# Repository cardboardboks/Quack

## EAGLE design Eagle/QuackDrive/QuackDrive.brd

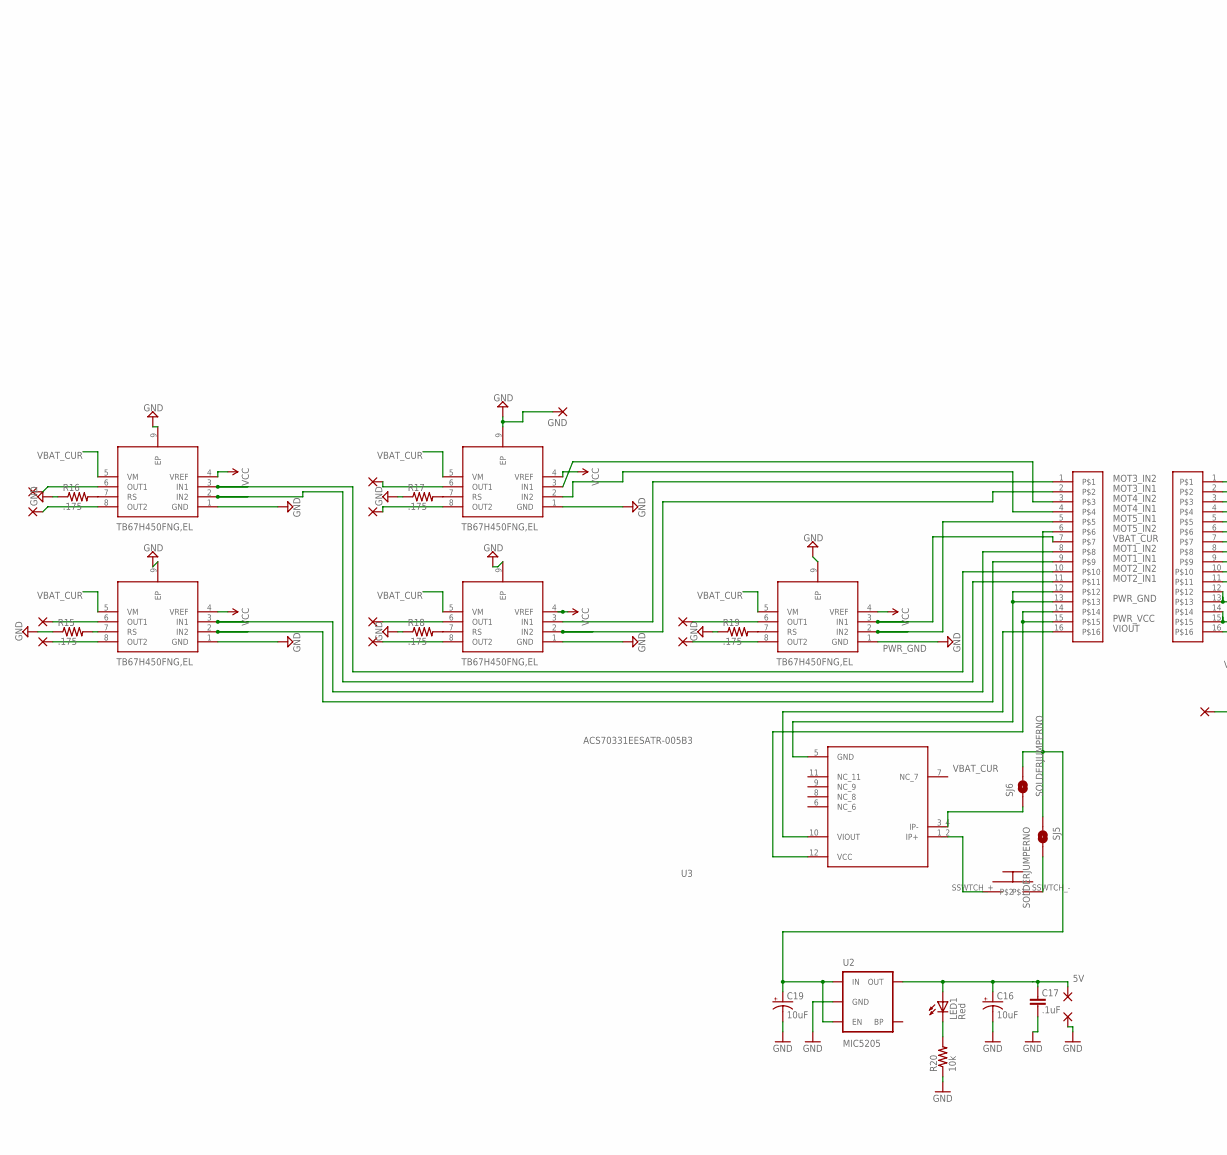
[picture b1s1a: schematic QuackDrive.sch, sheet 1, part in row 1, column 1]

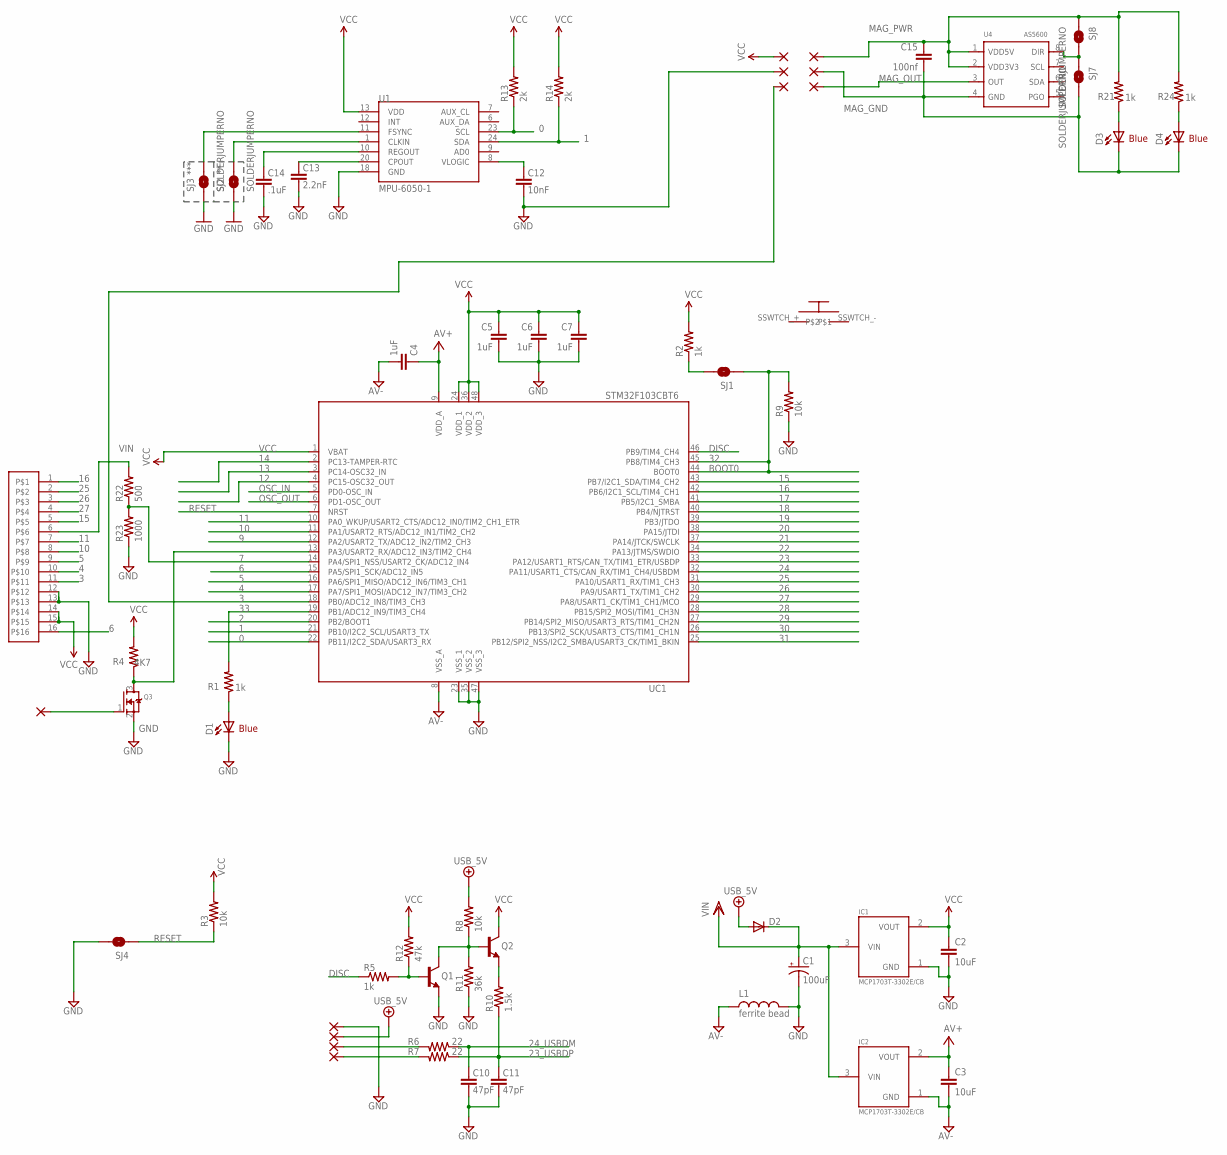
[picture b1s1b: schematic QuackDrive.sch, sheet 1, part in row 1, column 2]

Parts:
C1: 100uF; EIA3216
C2, C3: 10uF; 0805
C4, C5, C6, C7: 1uF; C0402
C10, C11: 47pF; C0402
C12: 10nF; C0402
C13: 2.2nF; C0402
C14, C17: .1uF; C0402
C15: 100nf; C0402
C16, C19: 10uF; EIA3216
D1, D3, D4: Blue; LED-1206
D2: DIODESOD; SOD-323
GND: SMD5; SMD2,54-5,08
IC1, IC2: MCP1703T-3302E/CB; SOT23
IC4, IC6, IC8, IC10, IC12: TB67H450FNG,EL; SOIC127P600X175-9N
L1: ferrite bead; 0603
LED1: Red; 0603-LED-ALT1
PAD1, PAD2, PAD3, PAD5, PAD6, PAD8, PAD9, PAD10, PAD11, PAD12: WIREPADSMD1,27-254; SMD1,27-2,54
PAD4, PAD7, PAD13, PAD14, PAD15, PAD16, PAD17, PAD18, PAD19, PAD20, PAD21, PAD22, PAD23: SMD2; SMD1,27-2,54
Q1, Q2: NPN-BJT; SOT23
Q3: MOSFET-NREFLOW; SOT23
R1, R2, R5, R21, R24: 1k; C0402
R3, R8, R9, R20: 10k; C0402
R4: 4K7; C0402
R6, R7: 22; C0402
R10: 1.5k; C0402
R11: 36k; C0402
R12: 47k; C0402
R13, R14: 2k; C0402
R15, R16, R17, R18, R19: .175; C0402
R22: 500; C0402
R23: 1000; C0402
SJ1, SJ2, SJ3, SJ4, SJ5, SJ6, SJ7, SJ8: SOLDERJUMPERNO; SJ_2S-NO
U1: MPU-6050-1; QFN-24-4MM2
U2: MIC5205; SOT23-5
U3: ACS70331EESATR-005B3; XDCR_ACS70331EESATR-005B3
U4: AS5600; SOIC8-1.27-5X4MM
U$1, U$3: WM8952DKR; SOP80P420X355-16N
U$2, U$4: SSWTCH; SSWITCH
UC1: STM32F103CBT6; LQFP48

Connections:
0: R13.1, U1.23 (SCL), UC1.22 (PB11/I2C2_SDA/USART3_RX)
1: R14.1, U1.24 (SDA), UC1.21 (PB10/I2C2_SCL/USART3_TX)
2: UC1.20 (PB2/BOOT1)
3: PAD14.1, U$3.11, UC1.18 (PB0/ADC12_IN8/TIM3_CH3)
4: U$3.10, UC1.17 (PA7/SPI1_MOSI/ADC12_IN7/TIM3_CH2)
5: U$3.9, UC1.16 (PA6/SPI1_MISO/ADC12_IN6/TIM3_CH1)
5V: C16.A (+), C17.2, LED1.A, PAD21.1, U2.5 (OUT)
6: U$3.16, UC1.15 (PA5/SPI1_SCK/ADC12_IN5)
7: R22.1, R23.2, UC1.14 (PA4/SPI1_NSS/USART2_CK/ADC12_IN4)
9: UC1.12 (PA2/USART2_TX/ADC12_IN2/TIM2_CH3)
10: U$3.8, UC1.11 (PA1/USART2_RTS/ADC12_IN1/TIM2_CH2)
11: U$3.7, UC1.10 (PA0_WKUP/USART2_CTS/ADC12_IN0/TIM2_CH1_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)
12: UC1.4 (PC15-OSC32_OUT)
13: UC1.3 (PC14-OSC32_IN)
14: UC1.2 (PC13-TAMPER-RTC)
15: U$3.5, UC1.43 (PB7/I2C1_SDA/TIM4_CH2)
16: U$3.1, UC1.42 (PB6/I2C1_SCL/TIM4_CH1)
17: UC1.41 (PB5/I2C1_SMBA)
18: UC1.40 (PB4/NJTRST)
19: UC1.39 (PB3/JTDO)
20: UC1.38 (PA15/JTDI)
21: UC1.37 (PA14/JTCK/SWCLK)
22: UC1.34 (PA13/JTMS/SWDIO)
23: UC1.33 (PA12/USART1_RTS/CAN_TX/TIM1_ETR/USBDP)
23_USBDP: C11.2, R7.1, R10.1
24: UC1.32 (PA11/USART1_CTS/CAN_RX/TIM1_CH4/USBDM)
24_USBDM: C10.2, R6.1
25: U$3.2, UC1.31 (PA10/USART1_RX/TIM1_CH3)
26: U$3.3, UC1.30 (PA9/USART1_TX/TIM1_CH2)
27: U$3.4, UC1.29 (PA8/USART1_CK/TIM1_CH1/MCO)
28: UC1.28 (PB15/SPI2_MOSI/TIM1_CH3N)
29: UC1.27 (PB14/SPI2_MISO/USART3_RTS/TIM1_CH2N)
30: UC1.26 (PB13/SPI2_SCK/USART3_CTS/TIM1_CH1N)
31: UC1.25 (PB12/SPI2_NSS/I2C2_SMBA/USART3_CK/TIM1_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)
32: R9.2, SJ1.1, UC1.44 (BOOT0), UC1.45 (PB8/TIM4_CH3)
33: R1.2, UC1.19 (PB1/ADC12_IN9/TIM3_CH4)
+5V/2: D2.2 (A), PAD18.1, R8.2
AV+: C3.1, C4.1, IC2.2 (VOUT), UC1.9 (VDD_A)
AV-: C3.2, C4.2, IC2.1 (GND), L1.1, UC1.8 (VSS_A)
CLKIN1: SJ2.2, U1.1 (CLKIN)
DISC: R5.1, UC1.46 (PB9/TIM4_CH4)
FSYNC1: SJ3.2, U1.11 (FSYNC)
GND: C1.C (-), C2.2, C5.2, C6.2, C7.2, C10.1, C11.1, C12.1, C13.1, C14.1, D1.C, IC1.1 (GND), L1.2, PAD15.1, PAD17.1, Q1.2 (E), Q3.2 (S), R9.1, R11.1, R23.1, SJ2.1, SJ3.1, SJ4.2, U1.18 (GND), U$3.12, U$3.13, UC1.23 (VSS_1), UC1.35 (VSS_2), UC1.47 (VSS_3)
MAG_GND: C15.2, D3.C, D4.C, PAD4.1, SJ7.2, U4.4 (GND)
MAG_OUT: PAD13.1, U4.3 (OUT)
MAG_PWR: C15.1, PAD7.1, R21.2, R24.2, SJ8.1, U4.1 (VDD5V), U4.2 (VDD3V3)
MOT1_IN1: IC4.2 (IN2), U$1.9
MOT1_IN2: IC4.3 (IN1), U$1.8
MOT2_IN1: IC6.2 (IN2), U$1.11
MOT2_IN2: IC6.3 (IN1), U$1.10
MOT3_IN1: IC8.2 (IN2), U$1.2
MOT3_IN2: IC8.3 (IN1), U$1.1
MOT4_IN1: IC10.2 (IN2), U$1.4
MOT4_IN2: IC10.3 (IN1), U$1.3
MOT5_IN1: IC12.2 (IN2), U$1.5
MOT5_IN2: IC12.3 (IN1), U$1.7
unnamed: R2.1, SJ1.2
unnamed: D1.A, R1.1
unnamed: Q3.3 (D), R4.1, UC1.13 (PA3/USART2_RX/ADC12_IN3/TIM2_CH4)
unnamed: SJ5.2, U$2.SSWTCH_-
unnamed: C12.2, U1.8 (VLOGIC)
unnamed: C13.2, U1.20 (CPOUT)
unnamed: C14.2, U1.10 (REGOUT)
unnamed: IC12.8 (OUT2), PAD5.1
unnamed: IC6.7 (RS), R16.2
unnamed: IC12.6 (OUT1), PAD6.1
unnamed: IC8.6 (OUT1), PAD2.1
unnamed: IC8.8 (OUT2), PAD1.1
unnamed: IC10.6 (OUT1), PAD8.1
unnamed: IC10.8 (OUT2), PAD3.1
unnamed: IC6.6 (OUT1), PAD12.1
unnamed: IC6.8 (OUT2), PAD11.1
unnamed: IC4.6 (OUT1), PAD10.1
unnamed: IC4.8 (OUT2), PAD9.1
unnamed: IC10.7 (RS), R17.2
unnamed: IC8.7 (RS), R18.2
unnamed: IC12.7 (RS), R19.2
unnamed: IC4.7 (RS), R15.2
unnamed: D3.A, R21.1
unnamed: SJ7.1, SJ8.2, U4.8 (DIR)
unnamed: LED1.C, R20.2
unnamed: D4.A, R24.1
unnamed: Q2.2 (E), R10.2
unnamed: PAD19.1, R6.2
unnamed: PAD20.1, R7.2
unnamed: Q1.3 (C), Q2.1 (B), R8.1, R11.2
unnamed: Q1.1 (B), R5.2, R12.1
OSC_IN: UC1.5 (PD0-OSC_IN)
OSC_OUT: UC1.6 (PD1-OSC_OUT)
PWR_GND: C16.C (-), C17.1, C19.C (-), GND.1, IC4.1 (GND), IC4.9 (EP), IC6.1 (GND), IC6.9 (EP), IC8.1 (GND), IC8.9 (EP), IC10.1 (GND), IC10.9 (EP), IC12.1 (GND), IC12.9 (EP), PAD22.1, R15.1, R16.1, R17.1, R18.1, R19.1, R20.1, U2.2 (GND), U3.5 (GND), U$1.12, U$1.13
PWR_VCC: IC4.4 (VREF), IC6.4 (VREF), IC8.4 (VREF), IC10.4 (VREF), IC12.4 (VREF), U3.12 (VCC), U$1.14, U$1.15
RESET: R3.1, SJ4.1, UC1.7 (NRST)
SBUSIN: PAD23.1, Q3.1 (G)
VBAT_CUR: C19.A (+), IC4.5 (VM), IC6.5 (VM), IC8.5 (VM), IC10.5 (VM), IC12.5 (VM), SJ5.1, SJ6.1, SJ6.2, U2.1 (IN), U2.3 (EN), U3.3_4 (IP-), U$1.6
VBAT_IN: U3.1_2 (IP+), U$2.SSWTCH_+
VCC: C2.1, C5.1, C6.1, C7.1, IC1.2 (VOUT), PAD16.1, Q2.3 (C), R2.2, R3.2, R4.2, R12.2, R13.2, R14.2, U1.13 (VDD), U$3.14, U$3.15, UC1.1 (VBAT), UC1.24 (VDD_1), UC1.36 (VDD_2), UC1.48 (VDD_3)
VIN: C1.A (+), D2.1 (C), IC1.3 (VIN), IC2.3 (VIN), R22.2, U$3.6
VIOUT: U3.10 (VIOUT), U$1.16

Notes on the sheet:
BOOT0
Blue
***

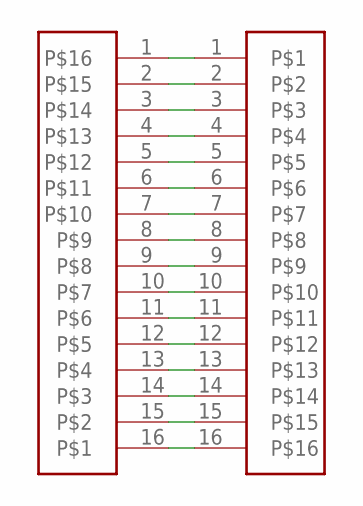
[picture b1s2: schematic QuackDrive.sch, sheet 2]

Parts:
U$5, U$6: WM8952DKR; SOP80P420X355-16N

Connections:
unnamed: U$5.1, U$6.1
unnamed: U$5.2, U$6.2
unnamed: U$5.3, U$6.3
unnamed: U$5.4, U$6.4
unnamed: U$5.5, U$6.5
unnamed: U$5.6, U$6.6
unnamed: U$5.7, U$6.7
unnamed: U$5.8, U$6.8
unnamed: U$5.9, U$6.9
unnamed: U$5.10, U$6.10
unnamed: U$5.11, U$6.11
unnamed: U$5.12, U$6.12
unnamed: U$5.13, U$6.13
unnamed: U$5.14, U$6.14
unnamed: U$5.15, U$6.15
unnamed: U$5.16, U$6.16

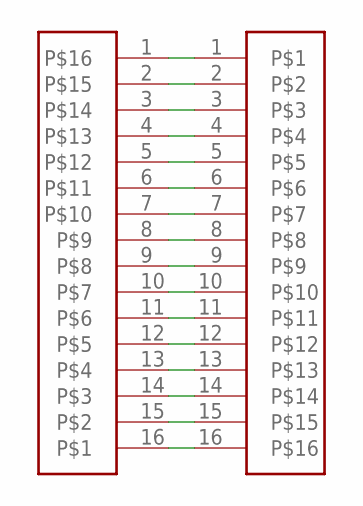
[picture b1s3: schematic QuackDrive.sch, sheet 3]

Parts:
U$7, U$8: WM8952DKR; SOP80P420X355-16N

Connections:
unnamed: U$7.1, U$8.1
unnamed: U$7.2, U$8.2
unnamed: U$7.3, U$8.3
unnamed: U$7.4, U$8.4
unnamed: U$7.5, U$8.5
unnamed: U$7.6, U$8.6
unnamed: U$7.7, U$8.7
unnamed: U$7.8, U$8.8
unnamed: U$7.9, U$8.9
unnamed: U$7.10, U$8.10
unnamed: U$7.11, U$8.11
unnamed: U$7.12, U$8.12
unnamed: U$7.13, U$8.13
unnamed: U$7.14, U$8.14
unnamed: U$7.15, U$8.15
unnamed: U$7.16, U$8.16

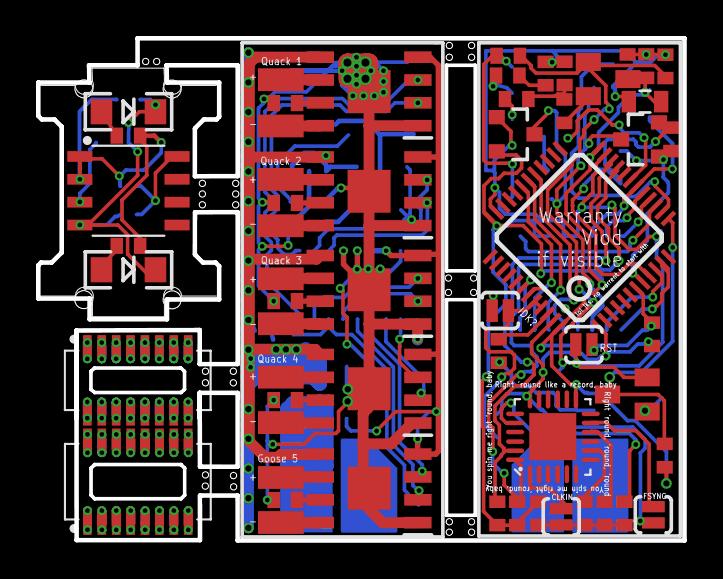
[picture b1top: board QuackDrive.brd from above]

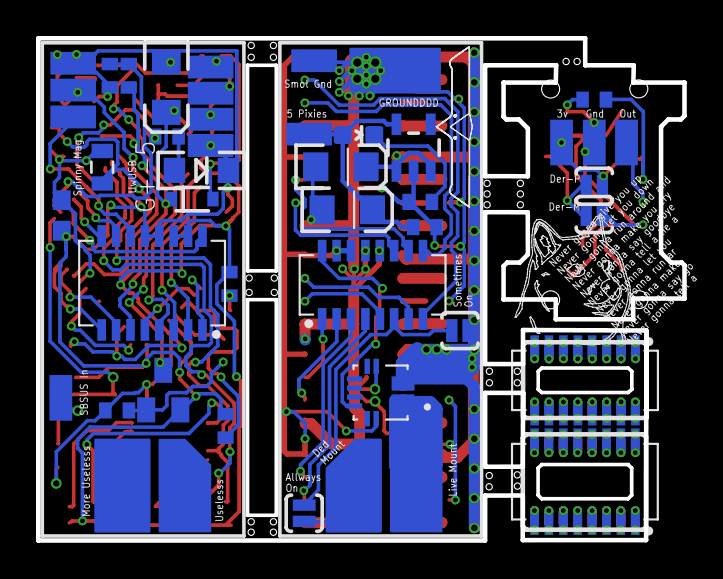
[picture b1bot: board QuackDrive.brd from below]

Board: 2 copper layers, 35.9 x 27.9 mm, 101 parts (44 on the bottom side), 111 nets.

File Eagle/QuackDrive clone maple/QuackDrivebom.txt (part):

Partlist exported from X:/Hadley/Documents/Quack/Quack/Eagle/QuackDrive/QuackDrive.sch at 9/11/2019 8:06 AM

Part  Value                Device               Package                   Description                                                                                                 DESCRIPTION                                                                                                 DIGI-KEY_PART_NUMBER DIGI-KEY_PURCHASE_URL                                                                                                                                                  HEIGHT MANUFACTURER_NAME MANUFACTURER_PART_NUMBER MF                       MOUSER_PART_NUMBER MOUSER_PRICE-STOCK                                                  MP                   PACKAGE                           POPULARITY RS_PART_NUMBER RS_PRICE-STOCK
C1    100uF                CAP_POL1206          EIA3216                   Capacitor Polarized                                                                                                                                                                                                                                                                                                                                                                                                                                                                                                                                                                                                                                                                  
C2    10uF                 CAP0805              0805                      Capacitor                                                                                                                                                                                                                                                                                                                                                                                                                                                                                                                                                                                                                                                                            
C3    10uF                 CAP0805              0805                      Capacitor                                                                                                                                                                                                                                                                                                                                                                                                                                                                                                                                                                                                                                                                            
C4    1uF                  CAP0402              C0402                     Capacitor                                                                                                                                                                                                                                                                                                                                                                                                                                                                                                                                                                                                                                                                            
C5    1uF                  CAP0402              C0402                     Capacitor                                                                                                                                                                                                                                                                                                                                                                                                                                                                                                                                                                                                                                                                            
C6    1uF                  CAP0402              C0402                     Capacitor                                                                                                                                                                                                                                                                                                                                                                                                                                                                                                                                                                                                                                                                            
C7    1uF                  CAP0402              C0402                     Capacitor                                                                                                                                                                                                                                                                                                                                                                                                                                                                                                                                                                                                                                                                            
C8    18pF                 CAP0402              C0402                     Capacitor                                                                                                                                                                                                                                                                                                                                                                                                                                                                                                                                                                                                                                                                            
C9    18pF                 CAP0402              C0402                     Capacitor                                                                                                                                                                                                                                                                                                                                                                                                                                                                                                                                                                                                                                                                            
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
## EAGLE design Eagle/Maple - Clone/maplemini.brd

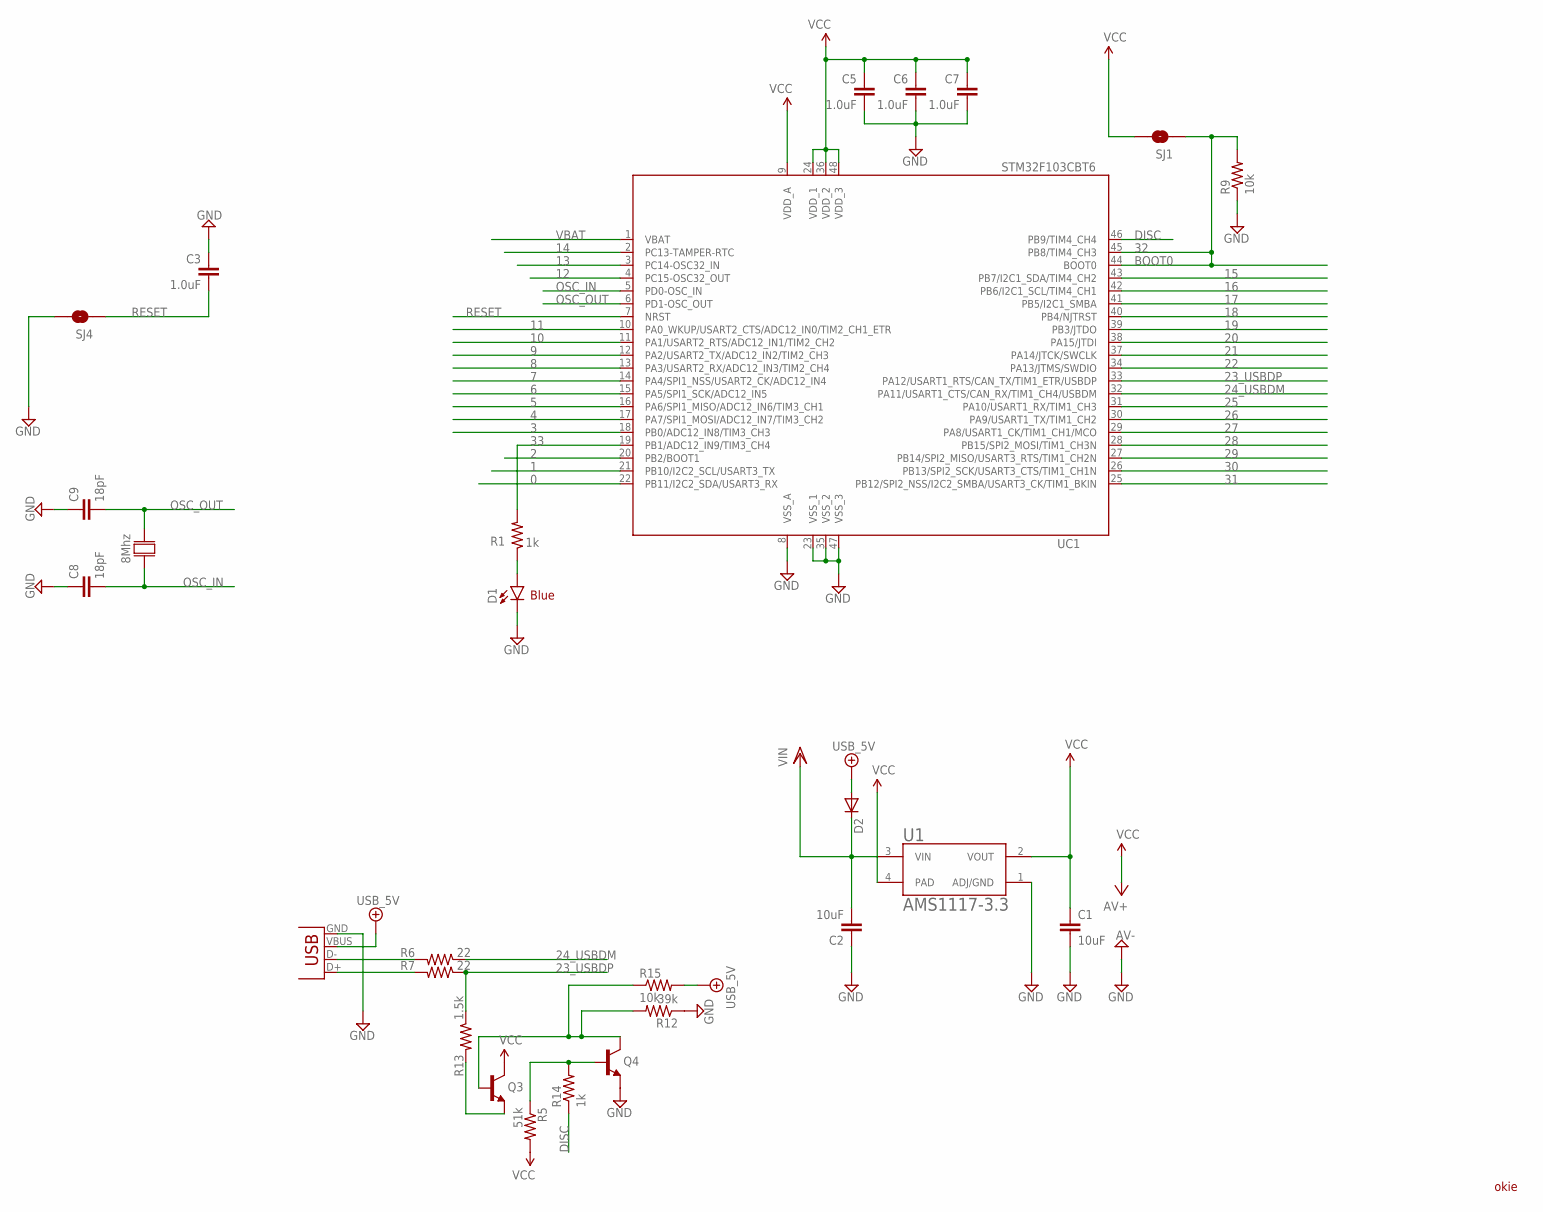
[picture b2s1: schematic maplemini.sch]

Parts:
C1, C2: 10uF; 0805
C3, C5, C6, C7: 1.0uF; 0603
C8, C9: 18pF; 0603
D1: Blue; LED-0603
D2: DIODESOD; SOD-323
Q3, Q4: NPN-BJT; SOT23
R1, R14: 1k; 0603
R5: 51k; 0603
R6, R7: 22; 0603
R9, R15: 10k; 0603
R12: 39k; 0603
R13: 1.5k; 0603
SJ1, SJ4: SOLDERJUMPERNO; SJ_2S-NO
U1: AMS1117-3.3; SOT229P700X180-4N
U$2: 8MHZCRYSTAL
UC1: STM32F103CBT6; LQFP48
X1: USB-MINIB

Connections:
0: UC1.22 (PB11/I2C2_SDA/USART3_RX)
1: UC1.21 (PB10/I2C2_SCL/USART3_TX)
2: UC1.20 (PB2/BOOT1)
3: UC1.18 (PB0/ADC12_IN8/TIM3_CH3)
4: UC1.17 (PA7/SPI1_MOSI/ADC12_IN7/TIM3_CH2)
5: UC1.16 (PA6/SPI1_MISO/ADC12_IN6/TIM3_CH1)
6: UC1.15 (PA5/SPI1_SCK/ADC12_IN5)
7: UC1.14 (PA4/SPI1_NSS/USART2_CK/ADC12_IN4)
8: UC1.13 (PA3/USART2_RX/ADC12_IN3/TIM2_CH4)
9: UC1.12 (PA2/USART2_TX/ADC12_IN2/TIM2_CH3)
10: UC1.11 (PA1/USART2_RTS/ADC12_IN1/TIM2_CH2)
11: UC1.10 (PA0_WKUP/USART2_CTS/ADC12_IN0/TIM2_CH1_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)
12: UC1.4 (PC15-OSC32_OUT)
13: UC1.3 (PC14-OSC32_IN)
14: UC1.2 (PC13-TAMPER-RTC)
15: UC1.43 (PB7/I2C1_SDA/TIM4_CH2)
16: UC1.42 (PB6/I2C1_SCL/TIM4_CH1)
17: UC1.41 (PB5/I2C1_SMBA)
18: UC1.40 (PB4/NJTRST)
19: UC1.39 (PB3/JTDO)
20: UC1.38 (PA15/JTDI)
21: UC1.37 (PA14/JTCK/SWCLK)
22: UC1.34 (PA13/JTMS/SWDIO)
23_USBDP: R7.1, R13.1, UC1.33 (PA12/USART1_RTS/CAN_TX/TIM1_ETR/USBDP)
24_USBDM: R6.1, UC1.32 (PA11/USART1_CTS/CAN_RX/TIM1_CH4/USBDM)
25: UC1.31 (PA10/USART1_RX/TIM1_CH3)
26: UC1.30 (PA9/USART1_TX/TIM1_CH2)
27: UC1.29 (PA8/USART1_CK/TIM1_CH1/MCO)
28: UC1.28 (PB15/SPI2_MOSI/TIM1_CH3N)
29: UC1.27 (PB14/SPI2_MISO/USART3_RTS/TIM1_CH2N)
30: UC1.26 (PB13/SPI2_SCK/USART3_CTS/TIM1_CH1N)
31: UC1.25 (PB12/SPI2_NSS/I2C2_SMBA/USART3_CK/TIM1_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)
32: R9.2, SJ1.1, UC1.44 (BOOT0), UC1.45 (PB8/TIM4_CH3)
33: R1.2, UC1.19 (PB1/ADC12_IN9/TIM3_CH4)
+5V/2: D2.2 (A), R15.2, X1.VBUS
DGND: C1.2, C2.1, C3.1, C5.2, C6.2, C7.2, C8.1, C9.1, D1.C, Q4.2 (E), R9.1, R12.1, SJ4.2, U1.1 (ADJ/GND), UC1.8 (VSS_A), UC1.23 (VSS_1), UC1.35 (VSS_2), UC1.47 (VSS_3), X1.GND
DISC: R14.1, UC1.46 (PB9/TIM4_CH4)
unnamed: D1.A, R1.1
unnamed: Q3.2 (E), R13.2
unnamed: Q4.1 (B), R5.1, R14.2
unnamed: Q3.1 (B), Q4.3 (C), R12.2, R15.1
unnamed: R6.2, X1.D-
unnamed: R7.2, X1.D+
OSC_IN: C8.2, U$2.P$1, UC1.5 (PD0-OSC_IN)
OSC_OUT: C9.2, U$2.P$2, UC1.6 (PD1-OSC_OUT)
RESET: C3.2, SJ4.1, UC1.7 (NRST)
VBAT: UC1.1 (VBAT)
VCC: C1.1, C5.1, C6.1, C7.1, Q3.3 (C), R5.2, SJ1.2, U1.2 (VOUT), U1.4 (PAD), UC1.9 (VDD_A), UC1.24 (VDD_1), UC1.36 (VDD_2), UC1.48 (VDD_3)
VIN: C2.2, D2.1 (C), U1.3 (VIN)

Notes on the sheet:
okie
BOOT0
Blue

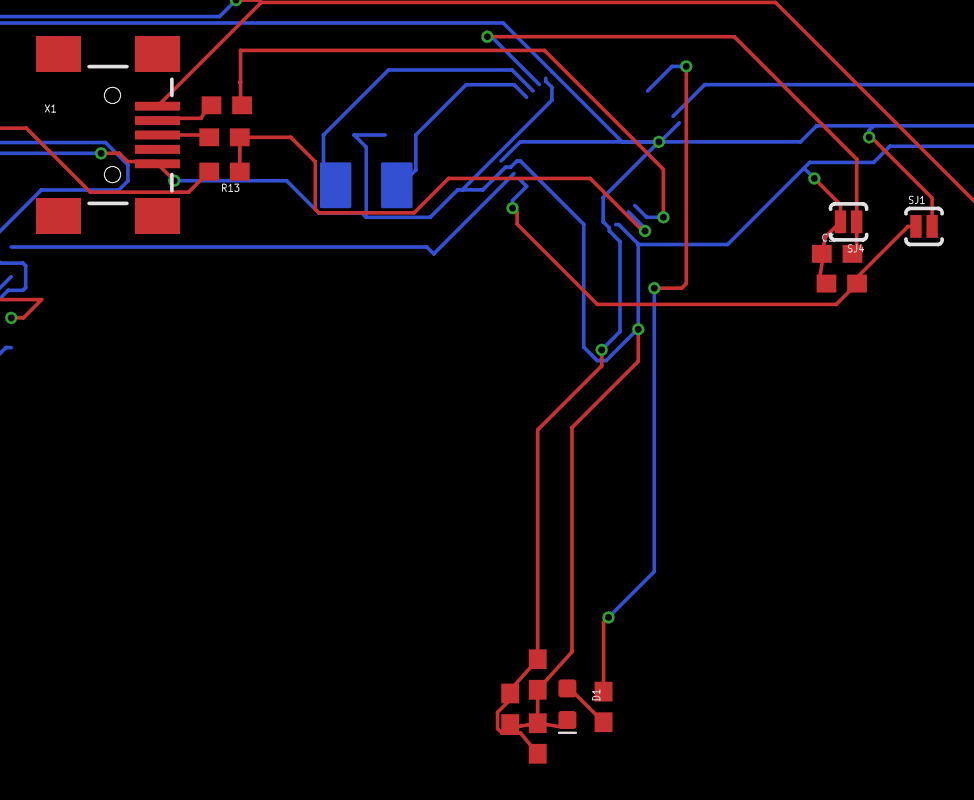
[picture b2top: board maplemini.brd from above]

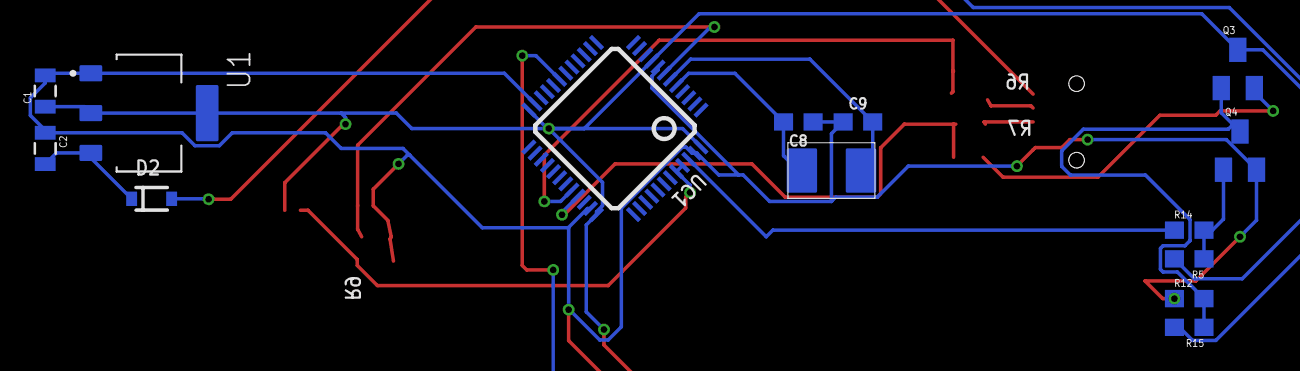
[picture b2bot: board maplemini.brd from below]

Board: 2 copper layers, 27 parts (14 on the bottom side), 18 nets.

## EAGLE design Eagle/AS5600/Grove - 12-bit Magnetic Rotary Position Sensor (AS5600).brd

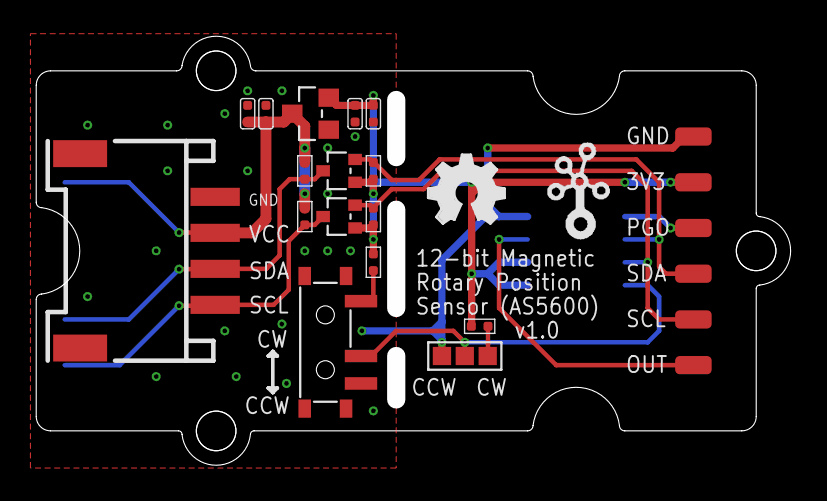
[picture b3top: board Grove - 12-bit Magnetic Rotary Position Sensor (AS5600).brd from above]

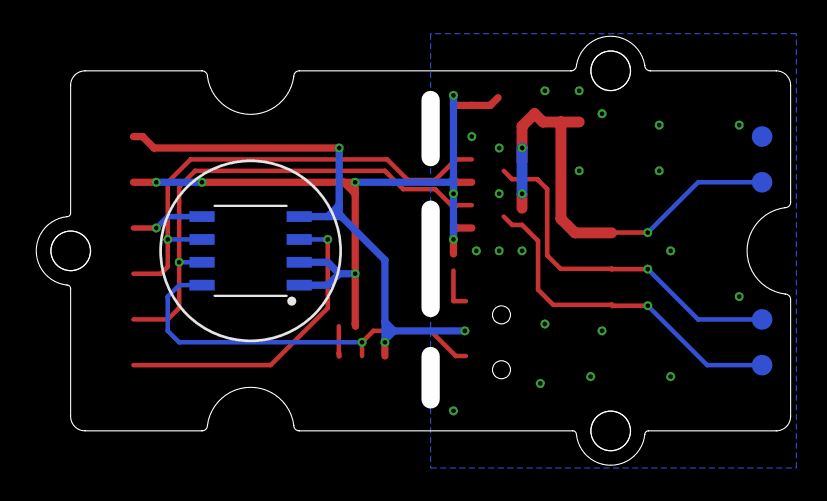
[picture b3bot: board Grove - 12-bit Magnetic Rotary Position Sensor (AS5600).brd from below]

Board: 2 copper layers, 40.9 x 22.8 mm, 30 parts (5 on the bottom side), 12 nets.

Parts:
C1, C3: 1uF; C0402
C2, C4: 100nF; C0402
J1: Grove; HW4-SMD-2.0-90D
JP1: DNP; 3P-SMD
LOGO1: LOGO-OSHW-FILLX0150-NT; OSHW_FILLX150_NOTEXT
Q1, Q2: 2N7002; SOT-323
R1, R2, R3, R4, R5, R6: 4.7k; R0402
SW1: SMD; SW7-SMD-L6.7X2.7X3.2MM
TP1, TP2, TP3, TP4: Test; TP-D45MIL
TP5, TP6, TP8, TP9, TP10, TP11: Test; TP-80X40MIL
U2: XC6206P332MR; SOT-23
U3: 20*40; GROVE-1*2-TEST-PLATFORM-TOP
U4: AS5600; SOIC8-1.27-5X4MM
U$4: LOGO-GROVETWIGLOGO_SMALL; GROVE-SILK-SMALL

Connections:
3V3: C3.2, C4.2, Q1.1, Q2.1, R1.2, R2.1, R3.1, R6.2, TP10.1, U2.2, U4.1, U4.2
GND: C1.1, C2.1, C3.1, C4.1, J1.4, J1.SS1, J1.SS2, JP1.00, SW1.3, SW1.SS1, SW1.SS2, SW1.SS3, SW1.SS4, TP4.T, TP11.1, U2.1, U4.4
unnamed: TP5.1, U4.3
unnamed: TP6.1, U4.5
unnamed: JP1.11, R6.1
unnamed: Q2.2, R3.2, TP9.1, U4.6
unnamed: JP1.MM, SW1.2, U4.8
unnamed: R1.1, SW1.1
unnamed: Q1.2, R2.2, TP8.1, U4.7
SCL: J1.1, Q1.3, R4.2, TP1.T
SDA: J1.2, Q2.3, R5.1, TP2.T
VCC: C1.2, C2.2, J1.3, R4.1, R5.2, TP3.T, U2.3

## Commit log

2019-10-22 added maple mini eagle files
2019-10-23 Started Eagel design
2019-10-23 Remove all but one current sens
2019-10-23 Liad out motor drives
2019-10-24 More layout
2019-10-24 3d stuff
2019-10-24 board thickness
2019-10-25 routed power board
2019-10-25 ipdate
2019-11-03 Maybe finished routing
2019-11-06 stuff
2019-11-10 Pictures and fixxes
2019-11-11 things
2019-11-13 new reference board desgn
2019-11-16 reworked off proper reference boards
2019-11-19 I did some things
2019-12-03 somthing
2020-05-24 Finished off missing bits
2020-05-24 Remove crystal, add Sbus inverter
2020-05-25 fixed silksceeen
2020-05-26 Removed castleation on raiser boards

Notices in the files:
parts and their libraries:
SparkFun-Capacitors: Licensing: Creative Commons ShareAlike 4.0 International - https://creativecommons.org/licenses/by-sa/4.0
